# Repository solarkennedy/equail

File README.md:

## Equail

## Description

Audubon society plush toys modified to activate on BTLE beacons.

## DEMO

## Explanation 

This is designed to interface with toys that run on batteries. The device uses
a NRF24L01+, set with a very specific destination address, on channels 37-39, 
which happen to overlap with some of the Bluetooth LE spec.

By configuring the radio to ignore stock (Nordic) crcs, and by implementing the 
BTLE CRC and whitening algorithms, we can interpret legitimate beacons and
respond to them.

## Prior Art

- Dmitry Grinberg's Bit Banging to [*send* a BTLE beacon](http://dmitry.gr/index.php?r=05.Projects&proj=15&proj=11.%20Bluetooth%20LE%20fakery)
- Florian Echtler's [BTLE library](https://github.com/floe/BTLE)
- Stanley Seow's [ATtiny85 port of the nrf library](https://github.com/stanleyseow/arduino-nrf24l01/)
- Nerd Ralph's hacks to run the nrf24 on [3 pins instead of 5](http://nerdralph.blogspot.ca/2014/01/nrf24l01-control-with-3-attiny85-pins.html) 

## Software Prerequisites

- [ATTiny Arduino Core](https://code.google.com/p/arduino-tiny/)
- Included Libraries installed
- Something to send a BTLE beacon (a linux computer)

## Hardware

- ATTiny85
- nrf24l01+
- An NPN transistor to switch on your device (2N3904)
- 3.3V Power supply (2X AA batteries)
- Some sort of ISP programmer

## Schematic

See the `schematic_eagle` folder for my first attempt at a schematic ever.

## Server-side

I use OpenWrt on a [TP-Link WR703N](http://wiki.openwrt.org/toh/tp-link/tl-wr703n)
plus an inexpensive [Bluetooth 4.0 dongle](http://www.ebay.com/itm/171213530142?ssPageName=STRK:MEWNX:IT&_trksid=p3984.m1497.l2649).

Combine this with an HTTP interface on an xinetd script and you have an API!

See `openwrt_setup` for more details on this. Having a dedicate computer that 
can respond to requests to generate beacons is cool.

Once you have server, you can emulate the [Audubon Singing Bird Clock](http://marketplace.audubon.org/products/audubon-singing-bird-clock)!

````
0 7  * * * /usr/sbin/send_beacon CalQuail
0 8  * * * /usr/sbin/send_beacon CaliGull
0 9  * * * /usr/sbin/send_beacon NrthCard
0 10 * * * /usr/sbin/send_beacon PrplFnch
0 11 * * * /usr/sbin/send_beacon EastBlue
0 12 * * * /usr/sbin/send_beacon WestMead
0 13 * * * /usr/sbin/send_beacon CaliWren
0 14 * * * /usr/sbin/send_beacon WillowPt
0 15 * * * /usr/sbin/send_beacon BrnPelic
0 16 * * * /usr/sbin/send_beacon CactusWr
0 17 * * * /usr/sbin/send_beacon WestMead
0 18 * * * /usr/sbin/send_beacon HermitTh
````

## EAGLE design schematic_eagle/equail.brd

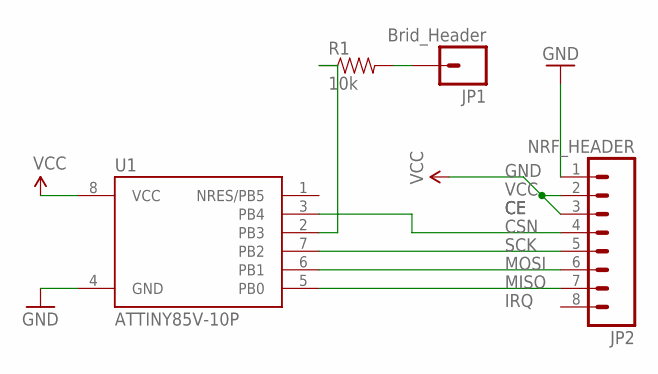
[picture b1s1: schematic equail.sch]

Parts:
JP1: Brid_Header; 1X01
JP2: NRF_HEADER; 1X08_PIN1_NO_SILK
R1: 10k; 1/6W-RES
U1: ATTINY85V-10P; PDIP08_300MIL

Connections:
GND: JP2.1, U1.4 (GND)
unnamed: JP1.1, R1.2
unnamed: R1.1, U1.2 (PB3)
unnamed: JP2.4, U1.3 (PB4)
unnamed: JP2.7, U1.5 (PB0)
unnamed: JP2.6, U1.6 (PB1)
unnamed: JP2.5, U1.7 (PB2)
VCC: JP2.2, JP2.3, U1.8 (VCC)

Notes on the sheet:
GND
VCC
SCK
MOSI
MISO
IRQ
CSN

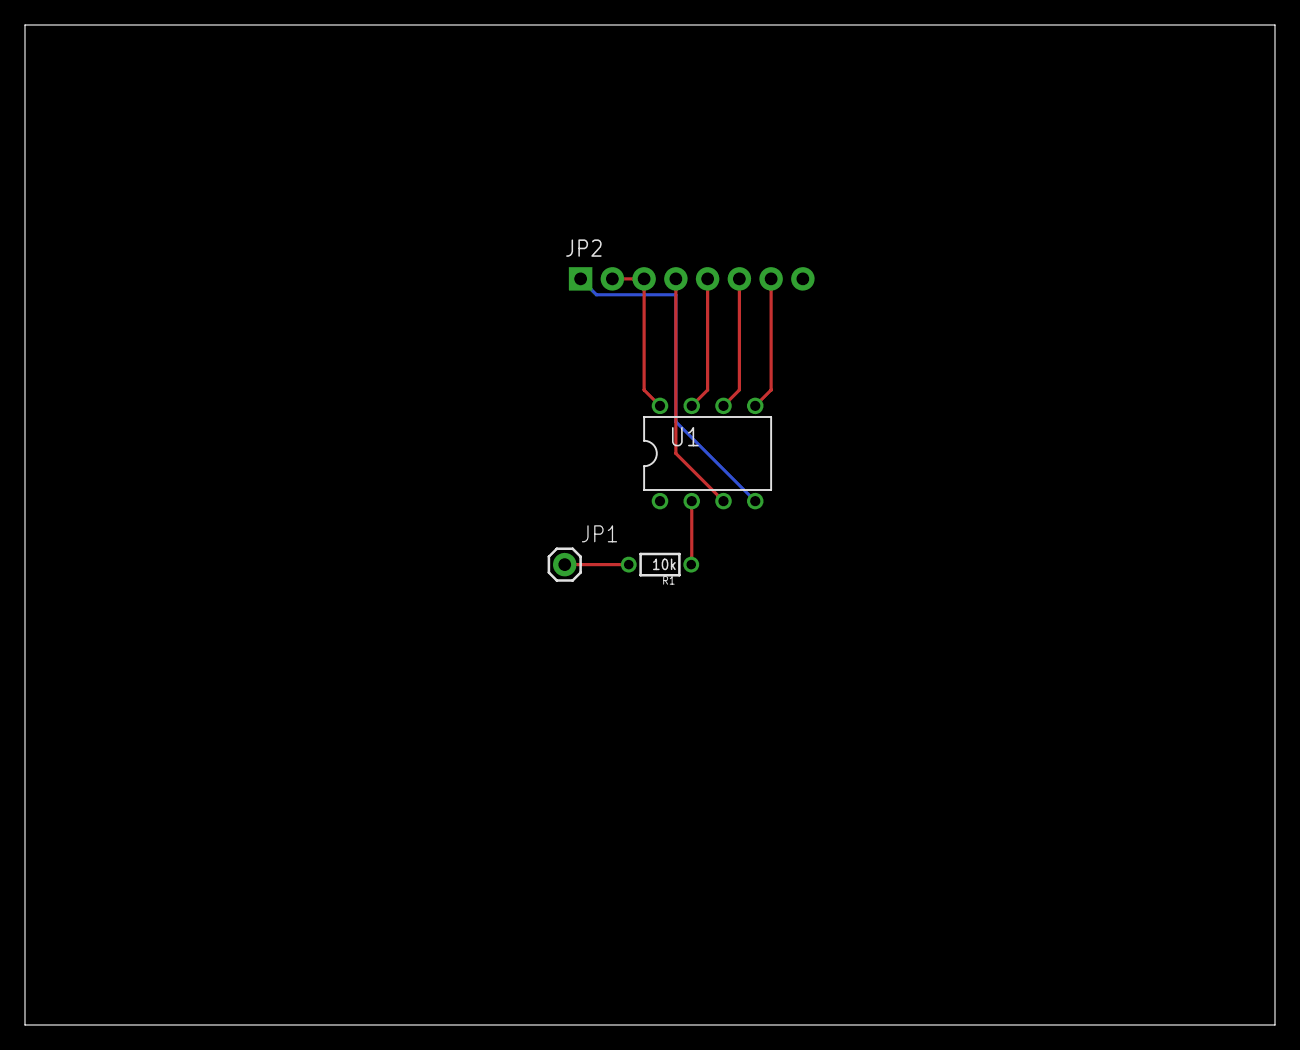
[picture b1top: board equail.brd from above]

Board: 2 copper layers, 100.0 x 80.0 mm, 4 parts (0 on the bottom side), 8 nets.

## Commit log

2014-05-18 Added linux utils for sending beacons
2014-05-18 Added sketch to see debug output
2014-05-18 Added modified libraries for attiny85
2014-05-18 Ignore trash
2014-05-18 Added readme
2014-05-18 Added license
2014-05-18 For ourselves to use pin 7 as the CE pin
2014-05-18 Less verbose on sendbeacon
2014-05-18 First code that sleeps to save poweR
2014-05-18 Reset after watchdog
2014-05-18 Added production firmware version
2014-05-18 Documented readme a bit
2014-05-25 Make the production firmware properly wait with the right timeouts
2014-05-31 Added install instructions
2014-05-31 Added equail xinetd stuff
2014-05-31 Added actual cgi scripts
2014-05-31 Make production firmware work correctly for equail sound module
2014-06-14 Whoops, hardcoded foobar in send_beacon
2014-06-14 Try to better understand bad CRC outputs
2014-06-14 Now with fuzzy name matching for lossy packets
2014-06-21 Added accuracy script
2014-06-21 Increase beacon timeout to 10s
2014-06-21 Make the production firmware sleep less frequently
2014-06-22 Fix seconds => minutes in accuracy script
2014-06-25 Trying fancier watchdog tactics
2014-06-28 Made the http responder more user friendly
2014-06-28 Modify send_beacon to be more http compliant
2014-06-28 Set conservative limits on xinetd usage
2014-06-28 Make send_beacon more verbose
2014-06-30 Made the send beacon script html aware
2014-07-05 No more flashing for production to save power
2014-07-09 Removed unused is_my_name function
2014-07-09 Cleaned up watchdog code
2014-07-09 Removed unused flash function for production
2014-07-09 Added broadcast function
2014-07-09 Added timeout to the http wrapper
2014-07-12 Fix broadcast bug
2014-07-13 Added http timeouts to send_beacon_http
2014-07-14 Updated readmes
2014-07-14 Added eagle schematic
2014-07-14 Added...... pictures
2014-07-20 Updated schematic to include extra capacitor
2014-07-20 Added debug firmware
2014-07-20 Added some finished pictures
2015-02-02 fix send_beacon
2015-02-02 Added ibeacon scan

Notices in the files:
parts and their libraries:
SparkFun-Passives: Licensing: Creative Commons ShareAlike 4.0 International - https://creativecommons.org/licenses/by-sa/4.0
